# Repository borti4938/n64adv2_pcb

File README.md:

N64 Advanced 2 (PCB)
---

This repository contains all you need files to build your own DIY N64 Advanced board.
Firmware is supplied in another repository.

Please don't ask me for selling a modding.
I either sell some prototypes on some forums marketplaces (which is very unlikely) or I don't have any of the boards.
This is a complete DIY modding project.
Everybody is on his own here.

**WARNING:**
This is an advanced DIY project if you do everything on your own.
You need decent soldering skills.
The FPGA ad Video transmitter have 0.5mm fine pitch with 144pins and 64pins, respectively, and each has an exposed pad below the IC, which has to be soldered to the PCB.
Furthermore, the clocking chip is in a 24-QFN package where the pins are partwise below the IC.
It also has an exposed pad.
Next to it on the board there are some SMD1206 resistor and ferrite bead arrays.

One note on KiCad: please do not use version 7 and stay with version 6.xx.yy, if you want to edit the PCB.
I have to adapt the design files first before there are working as intended in version 7.
Thanks!

## Table of Contents

- [Checklist](https://github.com/borti4938/n64adv2_pcb#checklist-how-to-build-the-project)
- [Assembly](https://github.com/borti4938/n64adv2_pcb#assembly)
- [PCB Specs](https://github.com/borti4938/n64adv2_pcb#pcb-specs)
- [Installation](https://github.com/borti4938/n64adv2_pcb#installation)
  - [1. Open the Console](https://github.com/borti4938/n64adv2_pcb#1-open-the-console)
  - [2. Preparation](https://github.com/borti4938/n64adv2_pcb#2-preparation)
  - [3. Solder Work](https://github.com/borti4938/n64adv2_pcb#3-solder-work)
  - [4. Testing Installtion](https://github.com/borti4938/n64adv2_pcb#4-testing-installation)
  - [5. Put Everything Together](https://github.com/borti4938/n64adv2_pcb#5-put-everything-together)
- [Installation with UltraPIF](https://github.com/borti4938/n64adv2_pcb#installation-with-ultrapif)
- [Jumper Description](https://github.com/borti4938/n64adv2_pcb#jumper-description)

## Checklist: How to build the project

- Use PCB files to order your PCBs. You need the order the main PCB. If you plan to have a clean install, you need to order a flexible PCB, too. You can opt for a fully custom flex-PCB or a partial flex-PCB where you run a FFC cable from flex to main PCB. Important PCB specifications are provided in the [BOM](./doc/n64adv2_BOM.xlsx).
  - Main PCB: either [KiCAD-PCB design file](./pcbs/main/n64adv2.kicad_pcb) or [Gerber files](./gerber/main/)
  - Full Flex PCB: either [KiCAD-PCB design file](./pcbs/flex/rcp2n64adv2.kicad_pcb) or [Gerber files](./gerber/full_flex/)
  - Partial Flex PCB: either [EAGLE-PCB design file](./pcbs/flex/rcp2fpc_v5.brd) or [Gerber files](./gerber/part_flex/)
- If you plan to use solder paste, do not forget to order a stencil for top and bottom, too
- Source the components you need, e.g. from Mouser or Digikey.
  The BOM is available in [here](./doc/n64adv2_BOM.xlsx).
- If you want to use a assembly service (PCBA), you have to generate position files and BOM (in format as the fab requests it) out of the PCB design files. For JLCPCB e.g., there is a [KiCad plugin](https://github.com/Bouni/kicad-jlcpcb-tools) available (which I yet didn't test).
- Wait for everything to arrive
- Assemble your PCB if you haven't use a PCBA service
- Flash the firmware ([firmware releases](https://github.com/borti4938/n64adv2_fw/releases)) after installing:
  - Use the POF programming file named n64adv2\__fpga-device_.pof
  - Using the intelFPGA programmer, JTAG chain is initialized by loading POF file
  - Select CFM0 and UFM for program and verify
  - N64 needs to be powered for flashing
  - Power cycle the N64 after flashing

## PCB Specs

- **Main-PCB** Use PCB files (either [KiCAD-PCB design file](./pcbs/main/n64adv2.kicad_pcb) or [Gerber files](./gerber/main/)) to order your own PCB with following specs (might be not comprehensive)  
  - Size: 89.6mm x 80.0mm
  - Layer: 4
  - FPC thickness: 1.6mm
  - Min hole size: dia 0.3mm / ring 0.6mm or lower
  - Min trace width / spacing: 0.2mm
- **Flex-PCB** Use PCB files (either [KiCAD-PCB design file](./pcbs/flex/rcp2n64adv2.kicad_pcb) or [Gerber files](./gerber/full_flex/)) to order your own PCB with following specs (might be not comprehensive)  
  - Size: 129.6mm x 25.0mm
  - Layer: 2
  - FPC thickness: 0.15mm \[1\]
  - Min hole size: dia 0.25mm / ring 0.45mm or lower
  - Min trace width / spacing: 0.2mm
  - Stiffener: PI top + bottom
  - Stiffener thickness: 0.15mm \[1\]

\[1\] You may have to vary FPC thickness and stiffener thickness depending on the prototype service you are going with. E.g., on my last order I opted for 0.12mm PCB thickness and 0.225mm polyimide thickness.

## Assembly

If you have all components available, you can start assembly your board.
You can use the [interactive BOM](./doc/n64adv2_main_ibom.html), which helps you organizing your work.
It is just a matter of time and effort to assembly everything.

Note that the FPGA has an exposed pad, which needs a good connection.
Otherwise, the FPGA will not boot at all.
Preheat the FPGA with a hot air gun and solder the exposed pad from bottom if you do not use solder paste.
If you only have your solder iron, apply heat from bottom.
You must be patient at this point as there are large GND planes around the FPGA.
You may check the FPGA temperature with your finger on the top side (once it gets too hot to touch, you may stop for soldering for a moment).
Do the same with the other chips which have an exposed pad (U2 and U4).

If you populate X2 with the THT variant, which is the JTAG connector, please short the pins such that they are flush at the bottom side.
Otherwise, the PCB might be lifted in its position which produces unnecessary mechanical stress on PCB and HDMI connector.

Using non-clean flux (rosin based) is obviously recommended.
Even though it is "non-clean" I recommend cleaning everything afterwards (just for the visual finish).

Please double check everything for shorts once you finished your work.
Very important is that the power supply trace do not short to GND.
- 5V against GND (e.g. at input pads)
- 3.3V against GND (e.g. at input pads)
- 2.5V against GND (e.g. at C14)
- 2.5V against GND (e.g. at C15)
- 3.3V against GND (e.g. at C132)
- 1.8V against GND (e.g. at C122)

## Installation

### 1. Open the console

- Remove Jumper Pak / Expansion Pak
- Remove screws from bottom side of the console  
(needs a 4.5mm gamebit tool)
- Lift top housing
- remove inner screws as marked  
(in very last consoles made the heat sink design changed slightly)
- pull out the mainboard
- remove heat sink and RF shield
- **Hint** Now you have the chance to clean up your N64 shell

(image by Zerberus (circuit-board.de user))

### 2. Preparation

It is possible to do a cut or a no-cut installation.
You will need the following parts for it:

1. N64Adv2 PCB
2. Flex Cable
3. Two to four of washers (M3)
4. Thermal pad
  - Cut Mod: appr. 1mm to 1.5mm thickness
  - No Cut Mod: appr. 2.5mm to 3.0mm thickness
5. 3D printed parts:
  - Cut Mod: [USB port round filler](./prints_3d/HalfCut/N64Adv2_USB_RoundFiller.stl), [JTAG spacer](./prints_3d/HalfCut/N64Adv2_JTAG_Spacer.stl) and [MultiOut replacement](./prints_3d/HalfCut/N64Adv2_MultiOut_HalfCut.stl)
  - No Cut Mod: [PCB lift bracket](./prints_3d/NoCut/N64Adv2_PCB_lift.stl) and [MultiOut replacement](./prints_3d/NoCut/N64Adv2_MultiOut_NoCut.stl)

#### 2.1 Shell Preparation Cut Mod

The bottom shell needs a cutout at the MultiOut port.

Mark the place you need to file with either the N64Adv2 PCB or the 3D printed MultiOut replacement.

File down the shell within your markings until the N64Adv2 sits flush on the shell floor.
Consider a tiny space below the HDMI connector.
Cleanup the shell and place the 3D printed parts into the shell.
Make a final fit test as shown.

#### 2.2 Shell Preparation No Cut

There is no need to cut the shell at all with this variant.
All you need is to remove the bottom RF shield from the N64 mainboard.

Place all 3D printed parts and make a fitting test as shown.

### 3. Solder Work

You have the options to either install everything with casual installation wires or using flex cables.
This is just a trade-off between personal installation effort and price.
Personally, I recommend using the flex cable.
Also with the flex cable you have the option to use a fully custom flex or a partial flex which just have a FFC connector on it to run a FFC cable from N64 to N64Adv2.

The instruction shows the installation with the fully custom flex.
The partial flex installation is similar, but not shown here.
The wired installation is not shown and not documented at all! (at least for the moment)

#### 3.1 Prepare the Flex Cable

The flex cable will be routed through the RF shield.
Close to it there are some capacitors.
Gently bend the flex cable between resistors and protection area (stiffener at top and bottom) as shown.
This relaxes routing with as low stress on the flex cable as possible.

If you opt for the partial flex, postpone this step until you have the partial flex installed (after step 3.2).
Measure where the FFC cable needs to be bend.
Apply some insulation tape for cable protection behind the bending area.

#### 3.2 Flex Cable Installation

Place the flex cable to the RCP-NUS output pins 6 to 28 as shown.
Put the solder area on to of the pins.
(However, putting them in front is also possible.)

Secure the cable with some kapton tape or with two solder joints.
Make sure that solder pads and pins are perfectly aligned.
The better the alignment is the easier is the solder work.

Apply solder to all pins.
Double check for shorts and good connections with a continuity tester of a digital multimeter.

Solder 3.3V, 5V, Reset and Controller legs to the N64 as shown.

Short summary:
- Solder the RCP connector side to the RCP-NUS as shown
  - first pin bottom – 6
  - last pin to – 28
- Connect 3.3V to the flex, e.g. taken from C141
- Connect 5V to the flex, e.g. taken from U13
- Connect Ctrl. and reset
  - reset from PIF-NUS pin 27
  - Controller from PIF-NUS pin 16  
  (Make sure that PIF-NUS pin 16 is connected to the middle pin of controller port 1, otherwise search for a suitable connection point)
- If you have a CPLD-based RGB mod, you can use J3 to setup VI-DeBlur on that mod over the N64Adv2
  - J3 has two pads: the left one (directly above the N64Adv2 logo) is the feedback signal, the other one is GND.
    Use a DMM if you are unsure (the GND pad has connection to any GND point on the N64 mainboard if flex is installed)
  - J3 signal pad is high on VI-DeBlur disabled and goes low if enabled

#### 3.2a Flex Cable Version 20231105 (and later)

With Version 20231105 the flex cable was redesigned at the ends to controller and reset connection at the PIF-NUS.

Changes were:
- No components anymore on the thin cable ends for easier handling
- Using a single gate buffer (U1) for the controller line is now mandatory.
- Backup pads for controller and reset connection of the thin cable breaks.
  If cable breaks you can simply cut off the broken cable end and route a separate wire from PIF pin to the backup pad.

#### 4. Testing Installation

At this point it is a good idea to test your installtion.

First you should check for some obvious short at the power rails, e.g. between 3.3V and GND, and between 5V and GND.
If the N64Adv2 board is connected with the flex, you can simply use the input pads on the N64Adv2 board.

Insert a game cartridge, connect HDMI and power, and turn on your N64!
**Important:** If you do not have heatsinks attached to your N64, only test for a brief moment.

Obviously, the firmware of the N64Adv2 must be flashed to the FPGA.

If you see a picture with game output and here some game audio, then everything might be ok.
It's a good idea to run the debug-screen for a quick check.
If something is not ok, the N64Adv2 hardware should boot into the debug screen by default.
Then you have to go for debugging your installation.

Additional information on flashing the firmware and how to debug with the debug screen, can be found the [firmwares repository](https://github.com/borti4938/n64adv2_fw).

#### 5. Put Everything Together

Secure your installation from shorts to the top RF shield with some insulation tape.
There is a risk for shorts where the controller leg of the full flex is routed.
Everything else is safe.

Place some washer (about 0.5mm to 1mm height) at the screw spots left and right of the N64Adv2 flex cable.
From my experience it is easier to secure them with some tape.
Close the RF shield of the N64 then.

Now connect the N64Adv2 PCB to the flex cable.
For the Cut-Mod, also place the bottom RF shield into its place of the N64.
The RF shield does not fit in the no-cut mod variant.

Put the thermal pad on top of the FPGA (U1) of the N64Adv2 board.
This helps with heat dissipation and holds the PCB in its place.

Put everything in the bottom shell.
Do not forget 3D printings.

Secure the N64 with two or three screws and make a small test to see if everything is working.
Do not forget to put in the Jumper Pak or Expansion Pak, otherwise you won't see a picture at all.

If everything works fine, close the whole shell.

## Installation with UltraPIF

This guide assumes that the UltraPIF will be installed after the N64Adv2.
However, other installation orders are possible, too - i.e. UltraPIF first and then N64Adv2 or both alongside.
There are not described, here.
For the ease of debugging, installation one after the other is always recommended.

Also, it is not described, how to open and close the N64.

### 1. Remove PIF-NUS

To remove the PIF-NUS, remove reset and controller connections, first.

The remove the PIF-NUS.

### 2. Install UltraPIF Adapter Board

Put the UltraPIF board into its place.
Connect clock and mode wires and if you want, the RGB led board.
More details on that can be found in the [UltraPIF Repository](https://github.com/jago85/UltraPIF_Hardware/wiki/Installation).

### 3. Connect Flex Cable

Once the UltraPIF Adapter sits in its place, you can reconnect the reset and controller connections of the flex cable.

For the controller connection, you can use the _CON_ pad on the adapter.

For the reset connection you have to go for pin 27 on the adapter.
**DO NOT USE THE _RST_ PAD!** as it acts as an input only.
Fallback functions won't be available if you do so.
Check the connection for shorts to adjacent pins.

### 4. Done

Put the UltraPIF on the UltraPIF Adapter board.

## Jumper Description

**IMPORTANT NOTE**  
Most jumpers are for development reasons and do not need to be touched at all.
This section is only for documentation purposes.

### On main N64Adv2 PCB

##### SJ1 to SJ4 (IO power supply for FPGA Bank 6 and 7)

**Section is outdated. Jumpers had been removed with version 20231119**

Bank B6 and B7 needs 2.5V VCCIO for current implementation.
Since N64Adv2_202200415, these jumpers are closed by default at 2.5V.
Earlier prototypes need a solder joint at 2.5V.
Do not touch 3.3V jumper as current implementation runs IO speed over specifications then.

##### SJ5 (5V power via USB port (X5))

**Section is outdated. Jumper has been removed with version 20231119**

- opened: (default) disable 5V power via USB
- closed: enable 5V power via USB

##### SJ6 (3.3V power via JTAG programmer X4)

**Section is outdated. Jumper has been removed with version 20231119**

- opened: (default) disable 3.3V power via JTAG programmer
- closed: enable 3.3V power via JTAG programmer

#### SJ11 (VI-DeBlur feedback)
- opened: disable feedback for fir flex prototypes
- closed: (default by a trace) feedback enabled

##### SJ31 (SRAM A12)

**Section is outdated. Jumper has been removed with version 20231119**

- opened: (default) use 8Mx16 memory
- closed: use 16Mx16 memory (firmware needs adaptation to work with 16Mx16 memory)

### On flex PCB

##### SJ1

**Section is outdated. Jumpers had been removed with version 20231105**

- opened: use with Schmitt trigger buffer (U1 and C1)
- closed: close jumper if you do not use Schmitt trigger buffer (U1 and C1)

##### J3
- VI-DeBlur feedback for CPLD based RGB mods (see installation section)

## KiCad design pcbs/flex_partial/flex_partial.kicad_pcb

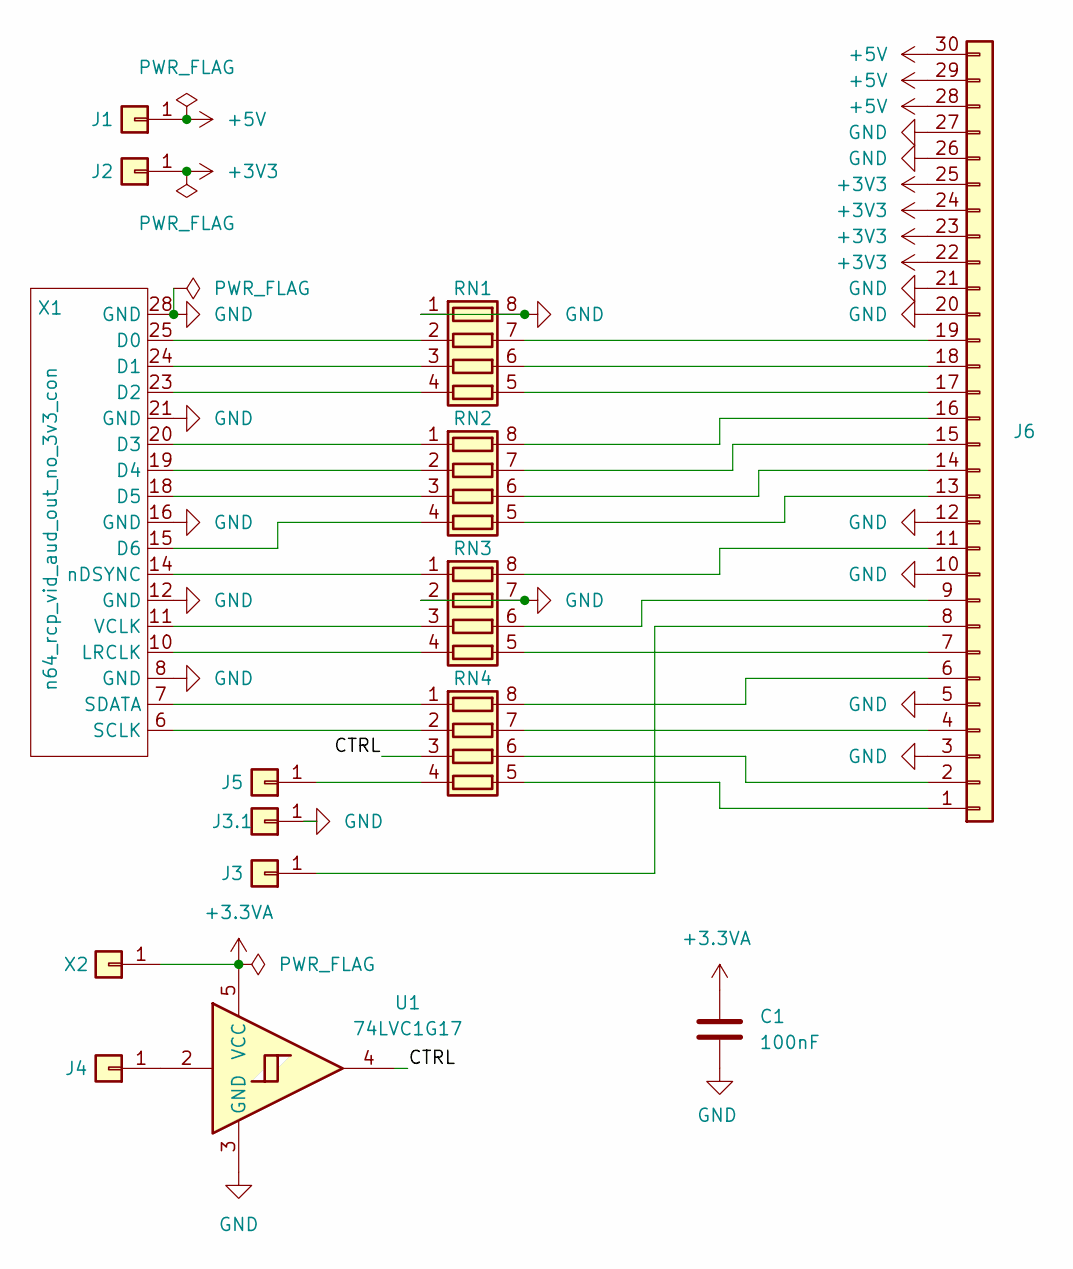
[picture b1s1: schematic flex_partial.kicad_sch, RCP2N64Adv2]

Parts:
C1: 100nF; C_0603_1608Metric_Pad1.08x0.95mm_HandSolder
J1, J2, J3, J3.1, J4, J5: Conn_01x01; TestPoint_Pad_D1.5mm
J6: Conn_01x30; FH12-30S-0.5SH
RN1, RN2, RN3, RN4: R_Pack04; R_Array_Convex_4x0603
U1: 74LVC1G17; TSOP-5_1.65x3.05mm_P0.95mm
X1: n64_rcp_vid_aud_out_no_3v3_con; Connector_RCP_Vi+Aud_Interface_no_3V3
X2: Conn_01x01; small

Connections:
+3.3VA: C1.1, U1.5 (VCC), X2.1
+3V3: J2.1, J6.22, J6.23, J6.24, J6.25
+5V: J1.1, J6.28, J6.29, J6.30
/CTRL: RN4.3 (R3.1), U1.4
GND: C1.2, J3.1.1, J6.3, J6.5, J6.10, J6.12, J6.20, J6.21, J6.26, J6.27, RN1.1 (R1.1), RN1.8 (R1.2), RN3.2 (R2.1), RN3.7 (R2.2), U1.3 (GND), X1.8 (GND), X1.12 (GND), X1.16 (GND), X1.21 (GND), X1.28 (GND)
unnamed: J3.1, J6.8
unnamed: J4.1, U1.2
unnamed: J5.1, RN4.4 (R4.1)
unnamed: J6.1, RN4.5 (R4.2)
unnamed: J6.2, RN4.6 (R3.2)
unnamed: J6.4, RN4.7 (R2.2)
unnamed: J6.6, RN4.8 (R1.2)
unnamed: J6.7, RN3.5 (R4.2)
unnamed: J6.9, RN3.6 (R3.2)
unnamed: J6.11, RN3.8 (R1.2)
unnamed: J6.13, RN2.5 (R4.2)
unnamed: J6.14, RN2.6 (R3.2)
unnamed: J6.15, RN2.7 (R2.2)
unnamed: J6.16, RN2.8 (R1.2)
unnamed: J6.17, RN1.5 (R4.2)
unnamed: J6.18, RN1.6 (R3.2)
unnamed: J6.19, RN1.7 (R2.2)
unnamed: RN1.2 (R2.1), X1.25 (D0)
unnamed: RN1.3 (R3.1), X1.24 (D1)
unnamed: RN1.4 (R4.1), X1.23 (D2)
unnamed: RN2.1 (R1.1), X1.20 (D3)
unnamed: RN2.2 (R2.1), X1.19 (D4)
unnamed: RN2.3 (R3.1), X1.18 (D5)
unnamed: RN2.4 (R4.1), X1.15 (D6)
unnamed: RN3.1 (R1.1), X1.14 (nDSYNC)
unnamed: RN3.3 (R3.1), X1.11 (VCLK)
unnamed: RN3.4 (R4.1), X1.10 (LRCLK)
unnamed: RN4.1 (R1.1), X1.7 (SDATA)
unnamed: RN4.2 (R2.1), X1.6 (SCLK)

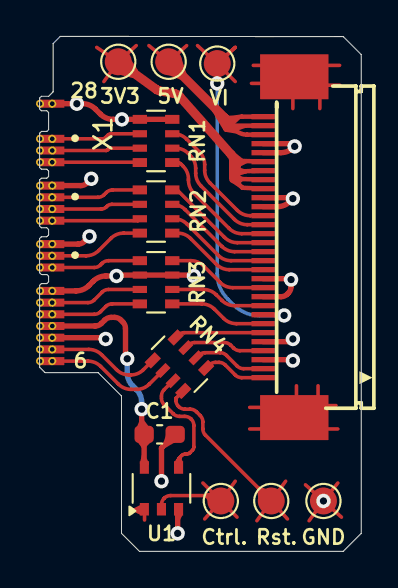
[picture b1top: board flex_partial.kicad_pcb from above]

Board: 2 copper layers, 17.9 x 28.6 mm, 15 parts (0 on the bottom side), 34 nets.

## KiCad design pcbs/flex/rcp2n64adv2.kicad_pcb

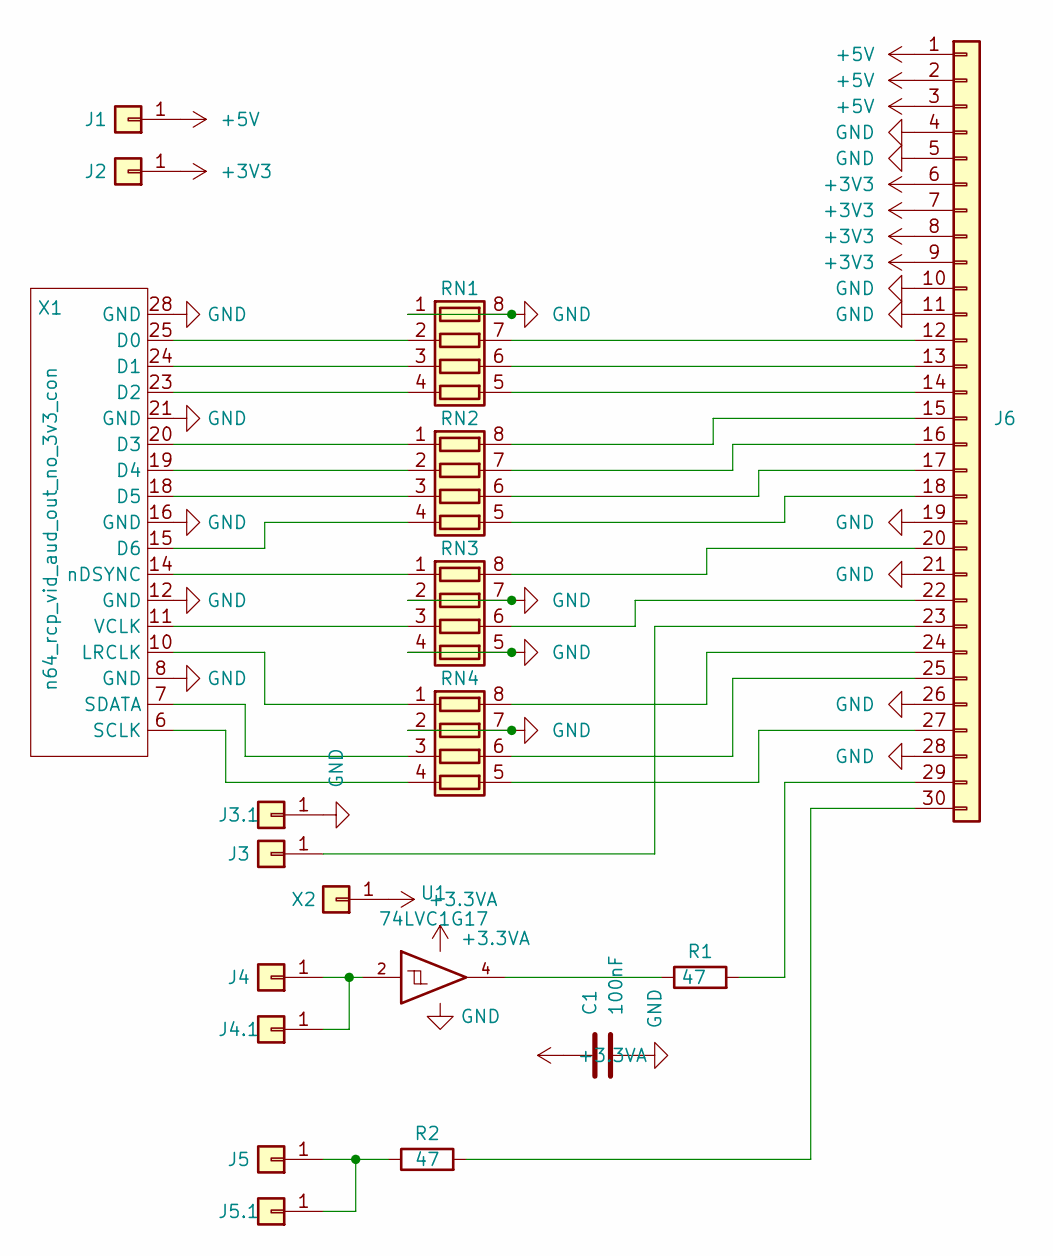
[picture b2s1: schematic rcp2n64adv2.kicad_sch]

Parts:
C1: 100nF; C_0603_1608Metric_Pad1.08x0.95mm_HandSolder
J1, J2: Conn_01x01; large
J3, J3.1, J4.1, J5.1: Conn_01x01; TestPoint_Pad_D1.5mm
J4, J5: Conn_01x01; medium
J6: Conn_01x30; EDGE-FH12-30S-0.5SH
R1, R2: 47; R_0603_1608Metric_Pad0.98x0.95mm_HandSolder
RN1, RN2, RN3, RN4: R_Pack04; R_Array_Convex_4x0603
U1: 74LVC1G17; TSOP-5_1.65x3.05mm_P0.95mm
X1: n64_rcp_vid_aud_out_no_3v3_con; Connector_RCP_Vi+Aud_Interface_no_3V3
X2: Conn_01x01; small

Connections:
+3.3VA: C1.1, U1.5 (VCC), X2.1
+3V3: J2.1, J6.6, J6.7, J6.8, J6.9
+5V: J1.1, J6.1, J6.2, J6.3
GND: C1.2, J3.1.1, J6.4, J6.5, J6.10, J6.11, J6.19, J6.21, J6.26, J6.28, RN1.1 (R1.1), RN1.8 (R1.2), RN3.2 (R2.1), RN3.4 (R4.1), RN3.5 (R4.2), RN3.7 (R2.2), RN4.2 (R2.1), RN4.7 (R2.2), U1.3 (GND), X1.8 (GND), X1.12 (GND), X1.16 (GND), X1.21 (GND), X1.28 (GND)
unnamed: J3.1, J6.23
unnamed: J4.1, J4.1.1, U1.2
unnamed: J5.1, J5.1.1, R2.1
unnamed: J6.12, RN1.7 (R2.2)
unnamed: J6.13, RN1.6 (R3.2)
unnamed: J6.14, RN1.5 (R4.2)
unnamed: J6.15, RN2.8 (R1.2)
unnamed: J6.16, RN2.7 (R2.2)
unnamed: J6.17, RN2.6 (R3.2)
unnamed: J6.18, RN2.5 (R4.2)
unnamed: J6.20, RN3.8 (R1.2)
unnamed: J6.22, RN3.6 (R3.2)
unnamed: J6.24, RN4.8 (R1.2)
unnamed: J6.25, RN4.6 (R3.2)
unnamed: J6.27, RN4.5 (R4.2)
unnamed: J6.29, R1.2
unnamed: J6.30, R2.2
unnamed: R1.1, U1.4
unnamed: RN1.2 (R2.1), X1.25 (D0)
unnamed: RN1.3 (R3.1), X1.24 (D1)
unnamed: RN1.4 (R4.1), X1.23 (D2)
unnamed: RN2.1 (R1.1), X1.20 (D3)
unnamed: RN2.2 (R2.1), X1.19 (D4)
unnamed: RN2.3 (R3.1), X1.18 (D5)
unnamed: RN2.4 (R4.1), X1.15 (D6)
unnamed: RN3.1 (R1.1), X1.14 (nDSYNC)
unnamed: RN3.3 (R3.1), X1.11 (VCLK)
unnamed: RN4.1 (R1.1), X1.10 (LRCLK)
unnamed: RN4.3 (R3.1), X1.7 (SDATA)
unnamed: RN4.4 (R4.1), X1.6 (SCLK)

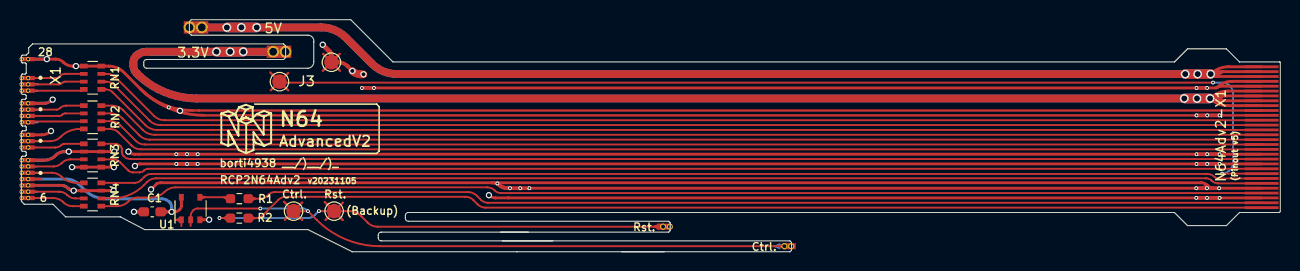
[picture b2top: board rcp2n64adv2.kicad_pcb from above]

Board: 2 copper layers, 129.6 x 23.9 mm, 19 parts (1 on the bottom side), 34 nets.

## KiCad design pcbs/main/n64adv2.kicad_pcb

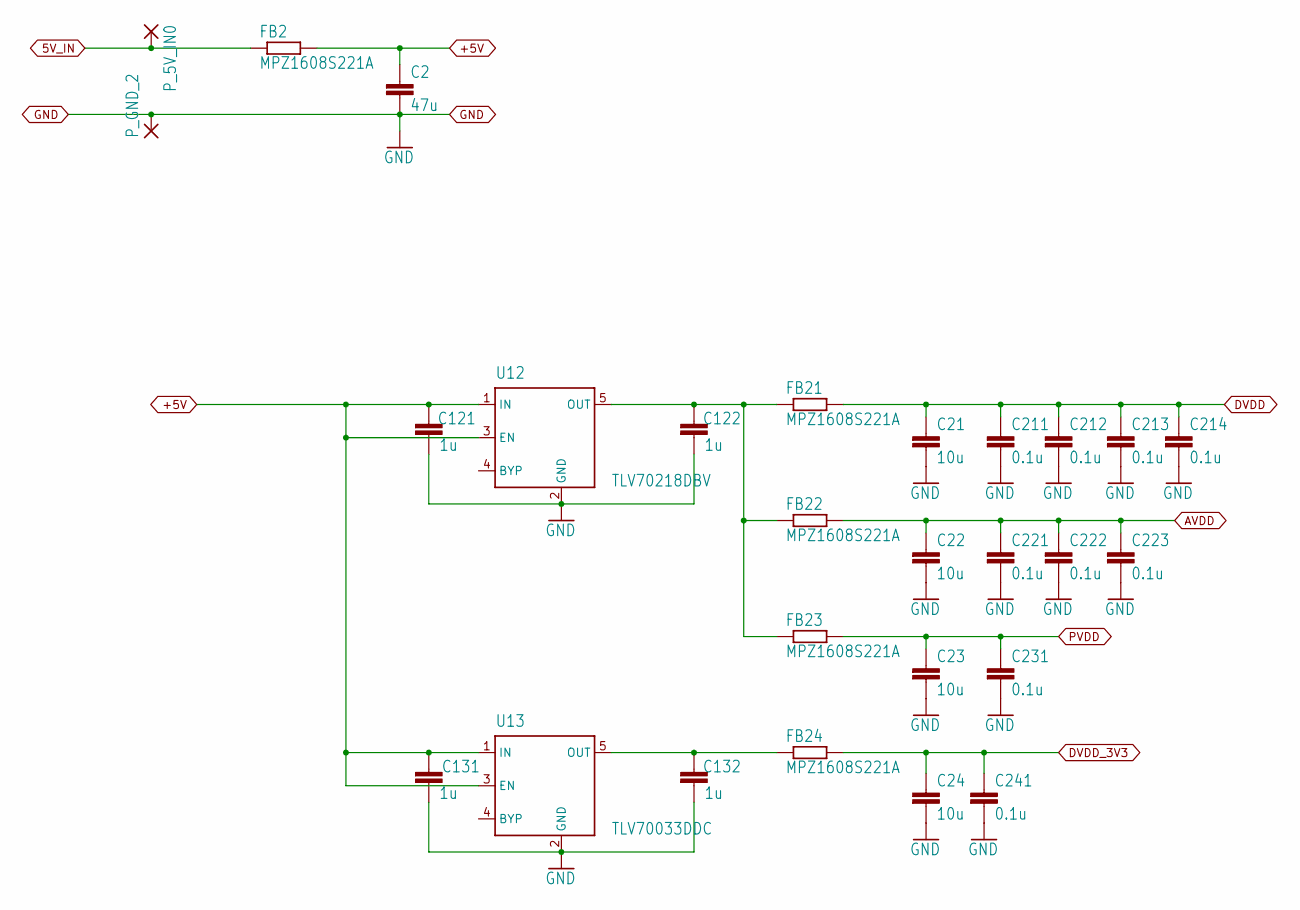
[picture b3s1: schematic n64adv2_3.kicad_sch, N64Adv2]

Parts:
C2: 47u; C0805
C21, C22, C23, C24: 10u; C0805
C121, C122, C131, C132: 1u; C0603
C211, C212, C213, C214, C221, C222, C223, C231, C241: 0.1u; C0603
FB2, FB21, FB22, FB23, FB24: MPZ1608S221A; R0603
P_5V_IN0: SMD2; SMD1,27-2,54
P_GND_2: SMD2; SMD1,27-2,54
U12: TLV70218DBV; SOT23-5
U13: TLV70033DDC; SOT23-5

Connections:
5V_IN: FB2.1, P_5V_IN0.1; also elsewhere on the board
+5V: C2.1, C121.1, C131.1, FB2.2, U12.1 (IN), U12.3 (EN), U13.1 (IN), U13.3 (EN); also elsewhere on the board
AVDD: C22.1, C221.1, C222.1, C223.1, FB22.2; also elsewhere on the board
DVDD: C21.1, C211.1, C212.1, C213.1, C214.1, FB21.2; also elsewhere on the board
DVDD_3V3: C24.1, C241.1, FB24.2; also elsewhere on the board
GND: C2.2, C21.2, C22.2, C23.2, C24.2, C121.2, C122.2, C131.2, C132.2, C211.2, C212.2, C213.2, C214.2, C221.2, C222.2, C223.2, C231.2, C241.2, P_GND_2.1, U12.2 (GND), U13.2 (GND); also elsewhere on the board
unnamed: C122.1, FB21.1, FB22.1, FB23.1, U12.5 (OUT)
unnamed: C132.1, FB24.1, U13.5 (OUT)
PVDD: C23.1, C231.1, FB23.2; also elsewhere on the board

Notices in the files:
pcbs/flex/rcp2n64adv2.kicad_pcb:
Schematic and PCB (c) 2021-2023 by Peter Bartmann
Licensed under CERN-OHL-W v2
CERN-OHL-W v2
